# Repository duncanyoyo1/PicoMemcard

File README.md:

# PicoMemcard

PicoMemcard allows you to build your own supercharged PSX Memory Card that can be connected to your computer via USB in order to transfer saves directly to/from your PSX. You can use it to repurpose broken/counterfeit Memory Cards creating a better one using only a Raspberry Pi Pico.

## Features

* Able to faithfully simulate PSX Memory Card
* USB connection to import/export saves
* Allows to copy saves to/from any other memory card (using original PSX file manager)
* Allows to play burned CDs (thanks to [FreePSXBoot])
* Cheaper than an original memory card
* Can store hudreds of memory card images

## Bill of materials

* **Raspberry Pi Pico** (around $5)
* One of:
    * Custom [PicoMemcard PCB](#picomemcard-pcb)
    * Broken/Counterfeit/Original PSX Memory Card (counterfeit ones can be found on AliExpress for around $2-3)
    * PSX/PS2 Controller Cable
    * CAT5 network cable and a bit of creativity.

Basically anything that will allow you to interface with the memory card slot pins will do. If you have a broken contoller you can cut off the cable and use that since controllers and memory cards share the same bus. Of course, plugging your memory card into the controller slot will prevent you from using 2 controllers at the same time.

[This guy] assembled one using a 3d-printed plastic shell and simple CAT5 network cable. I belive this is the cheapest method anybody has come up with until now.

In total building a PicoMemcard wil cost you less than buying a used original Memory Card!

## Video

## PicoMemcard PCB

These are the custom PCBs designed and manufactured specifically for this application. They are not strictly required but make it much easier to build PicoMemcard since you don't need to cut up another memory card and all the soldering pads are easily accessible. All you need to do is to solder the Pico/RP2040-Zero on top of the PCB using a soldering iron.

The Raspberry Pi Pico or RP2040-Zero must sit flush on top of the PCB, fortunately both the Pico and RP2040-Zero provide castellated holes that are easy to solder directly to the PCB's pads. You can use some electrical tape to hold the board in place while you solder the first pins.

I've created a new version of the original PCBs the major difference are:

* The general size is smaller
* A new micro SD card module is supported. This module is smaller, easier to solder and should solve some of the power related issues that were previously present
* Is fitted for the installation of phisical switches used to switch memory card when PicoMemcard+ is used in systems that do not support switching via controller input (e.g. all PS2 models).

The KiCad and Gerber files are available in the repository. If you want to support the project you can request a PCB [from here]. 
Keep in mind that with the PS2 support release that will eventually happen the PCB may undergo some additional changes before its design is finalized.

## PicoMemcard using Memory Card

Raspberry Pi Pico and RP2040-Zero require different pin usage for full compatibility.

The wiring diagrams below show how to build PicoMemcard by wiring respectively a Pico and an RP2040-Zero to a counterfeit memory card. For the other cases (wiring directly to the PSX or using a controller cable) the pins on Pico and RP2040-Zero are the same, the pinout of the PSX/controller can be found on [psx-spx]. The images show the bottom side of the memory card with the cover removed.

The dashed line on the PCB of the memory card is where you should cut a groove deep enough to disconnect the original circuitry from the traces. The yellow squares above the line indicate where you should scrape away the protective film in order to expose the copper traces and solder the wires onto them.

Finally the area at the bottom of the memory card is where you can cut a hole to feed the wires through connecting them to the Pico.
If you are using an RP2040-Zero you can also cut away part of the original Memory Card circuitry to fit it inside the original shell.

The connections in the PicoMemcard+ area are optional and only required if you want to build **PicoMemcard+** (using the optional MicroSD expansion board). Also remember to connect both ground and power to your SD card module (see [MicroSD Module](#microsd-module-for-picomemcard) section for more information).

## PicoMemcard vs PicoMemcard+

Since some features cannot be implmented when using only a Pico/RP2040-Zero but require additional hardware, I've decided to split the project in two versions:

* **PicoMemcard** simplest device to build, only requires a Raspberry Pi Pico / RP2040-Zero
* **PicoMemcard+** more complex and powerful device. Supports additional features such as multiple memory card images but requires additional hardware (namely the MicroSD SPI expansion board).

This approach was choosen because many people want a solution that is as cheap as possible and don't care about additional features. Conversely, others would like to have additional features even if it means spending a bit more money.

The current release of PicoMemcard+ additionally to all the features of PicoMemcard supports:

* Trasparent write-back: the sync operation performed to save new data no longer reults in the memory card appearing as if was briefly disconnected.
* Multiple memory card image switchable through controller input.

## MicroSD Module for PicoMemcard+

There are many variations of MicroSD expansion boards with different pinouts and interfaces. The only requirement for PicoMemcard+ is that the module must provide an SPI interface. SPI interfaces have at least the following pins:

* Chip Select (CS) (sometime also called Slave Select (SS)).
* Clock (SCK or CLK).
* Master Output Slave Input (MISO).
* Master Input Slave Output (MOSI).

In addition you will need to connect power and ground to your module, some modules are design to work with 5V others with 3.3V (or both), luckily for us both voltages are available on Pico and RP2040-Zero as shown in the schematic in the section [above](#picomemcard-using-memory-card). Some module provides additional pins that can be left disconnected.

The new versions of the PCB are designed to use small modules such as this one:

This is mainly due to the following reasons:

* It comes withouth pre-soldered headers which makes it easier to solder onto the PicoMemcard PCB.
* Its smaller form factor allows for more flexibility.
* It should have less power issue than prevously used modules.

A good source for these modules is Aliexpress, in general you can search for `MicroSD SPI Expansion Board` and buy the cheapest one you find.

## Installation

1. Download the latest [release] for your board (Raspberry Pi Pico and RP2040-Zero require different binaries).
2. While pressing the 'BOOTSEL' or 'BOOT' button on your board, plug it into your computer. 
3. Drag and drop the PicoMemcard release onto your Raspberry Pi Pico.
4. PicoMemcard should appear on your PC as a USB drive.
5. Upload a memory card image to your PicoMemcard.

## Transfering Data

Memory card images must be exactly 128KB (131072 bytes) in size. PicoMemcard and PicoMemcard+ only support files with `.MCR` extensions. However, `.MCR` and `.MCD` extensions are interchangable and can be converted to one another simply via renaming.
For other file formats, try using [MemcardRex] for converting to the desired output.

* **PicoMemcard** only supports a single image which must be named exactly `MEMCARD.MCR`.
* **PicoMemcard+** supports hundreds of images. Each image must be named `N.MCR` where `N` is an integer number (e.g. `0.MCR`, `1.MCR`...). On boot your previously loaded image will be reloaded, unless it's a fresh card then `0.MCR` will be loaded.

Inside `docs/images` you can find two memory card images. One has a couple of saves on it so you can test if everything works correctly, the other is completely empty.

## Switching/Creating Images

On **PicoMemcard+** you can switch the active memory card image with the following inputs:

* `START + SELECT + DPAD UP` will switch to the next image (e.g from `1.MCR` to `2.MCR`).
* `START + SELECT + DPAD DOWN` will switch to the previous image (e.g from `1.MCR` to `0.MCR`).

Additionally you can create a new empty memory card image (and automatically switch to it) by pressing  `START + SELECT + TRIANGLE`.

**Attention**: this method only works on PSX if the controller used to provide the input is plugged in the same slot as PicoMemcard (exactly under it). Using a controller from a different slot will have no effect.

Additionally this method does not work on PS2 Memory Cards and Controllers are wired on a different bus.

## Syncing Changes

Generally speaking, new data written to PicoMemcard (e.g. when you save) is permanently stored only after a short period of time (due to hardware limitation). The on board LED indicates whether all changes have been stored or not, in particular:

* On Rapsbery Pi Pico the LED will be on when all changes have been saved, off otherwise.
* On RP2040-Zero the LED will be solid green when all changes have been saved, red otherwise.

Unlike **PicoMemcard+** that tries to write new changes as soon as possible, **PicoMemcard** will generally do it only after a period of inactivity (around 5 seconds). If you want to force **PicoMemcard** to immediately sync you can press `START + SELECT + TRIANGLE`.

**Attention**: after you save your game, make sure to wait for the LED to be solid green before turning off the console otherwise you might lose your more recent progress!

## 3D-Printed Case

I've finally designed a 3D-printable case for the different PicoMemcard PCBs. It helps inserting correctly the PCB and ensuring that the the connection to the PSX is optimal. The same result, albeit more janky, can be achieved using a folded sheet of paper as a spacer.

The cases are designed following a minimalistic approach, they consist of a single piece which holds tightly the PCB using very small clips without requiring any additional hardware. To assemble it, simply slide in the PCB from the back of the case (opposite to the side connecting to the PSX). Cases for the fullsize PCB are designed to support the MicroSD expansion module.

Here is the download for the STL files:

* [Design by DanGiu](https://www.thingiverse.com/thing:5488778)

If you don't like this case you can check out other designs many people have already created! I've not tested them personally but here they are:

* [Design by brik1111](https://www.thingiverse.com/thing:5453156)
* [Design by bbsan2k](https://www.thingiverse.com/thing:5460187)

## Troubleshooting and LED Indicator

Generally speaking the onboard LED will provide a pretty good indication regarding the status of PicoMemcard.

In particular, the RP2040-Zero has RGB LED that provides a more clear output. The Pico on the other hand as only a green LED and different blinking patterns indicate different statuses.

### PicoMemcard Status

| Status | Pico | RP2040-Zero
| --- | --- | --- |
| Failed to read memory card image | Slow blinking led  | Red blinking led
| Data not fully synced (do not turn off PSX)| Led off | Red led (or flashing red and green) |
| Data synced | Led on | Green solid led |

### PicoMemcard+ Status

| Status | Pico | RP2040-Zero
| --- | --- | --- |
| Failed to read SD card | Blinking led  | Red blinking led
| Data not fully synced (do not turn off PSX)| Led off | Red led (or flashing red and green) |
| Data synced | Led on | Green solid led |
| Memory Card image changed | Three fast blinks | Single blue blink |
| Memory Card image not changed (end of list) | Nine fast blinks | Single orange blink |
| New Memory Card image created | Multiple very fast blinks | Single light blue blink |

## General Warnings

I would recommend to never plug PicoMemcard both into the PC (via USB) and the PSX at the same time! Otherwise the 5V provided by USB would end up on the 3.3V rail of the PSX. I'm not really sure if this could cause actual damage but I would avoid risking it.

If you really need to have the Pico plugged into both the USB and PSX (e.g. for debugging purposes), disconnect the 3.3V line from the VBUS pin. In this way you can power on the Pico using a simple USB phone charger or by plugging it into your PC.

As a disclamer, I don't take any responsability for what will happen to your console when using PicoMemcard/PicoMemcard+.

## Project Updates

### 5 February 2023

Sorry everybody but I've been quite inactive on the project lately. Due to a change of job IRL I have less time to work for the moment.
Anyway, behind the scenes I've been trying to add support for PS2 memory card but I'm afraid that will require the addition of an extra hardware component unless I am able to develop an efficient cacheing mechanisms or something similar. Anyway I'll keep working on it when I have free time. I have in mind many improvement for the project and I think the future of it is going to be exciting.

Special thanks to everybody that supported it so far! You are all amazing.

## Design

For people interested in understanding how PicoMemcard works I provide a more extensive explanation in [this post] (although now somewhat outdated).

## Thanks To

* [psx-spx] and Martin "NO$PSX" Korth - PlayStation Specifications and documented Memory Card protocol and filesystem.
* [Andrew J. McCubbin] - Additional information about Memory Card and Controller communication with PSX.
* [littlefs] - Filesystem designed to work on NOR flash used by many microcontrollers, including the Raspberry Pi Pico.
* [ChaN FatFS] - FAT filesystem implementation for embedded devices.
* [Scoppy] - Use your Raspberry Pi Pico as an oscilloscope, very cheap and accurate. Without this I would have not been able to debug many issues.
* [PulseView] - Used to import, visualize and manipulate the data from Scoppy on a PC.

[FreePSXBoot]: https://github.com/brad-lin/FreePSXBoot
[psx-spx]: https://psx-spx.consoledev.net/pinouts/#controller-ports-and-memory-card-ports
[Andrew J. McCubbin]: http://www.emudocs.org/PlayStation/psxcont/
[littlefs]: https://github.com/littlefs-project/littlefs
[ChaN FatFS]: http://elm-chan.org/fsw/ff/00index_e.html
[Scoppy]: https://github.com/fhdm-dev/scoppy
[PulseView]: https://sigrok.org/wiki/PulseView
[release]: https://github.com/dangiu/PicoMemcard/releases/latest
[this post]: https://dangiu.github.io/2022/05/13/picomemcard.html
[from here]: https://forms.gle/f6XHtz6W5fn5qDZV7
[This guy]: https://github.com/MrSVCD/PicoPSX_3D
[MemcardRex]: https://github.com/ShendoXT/memcardrex

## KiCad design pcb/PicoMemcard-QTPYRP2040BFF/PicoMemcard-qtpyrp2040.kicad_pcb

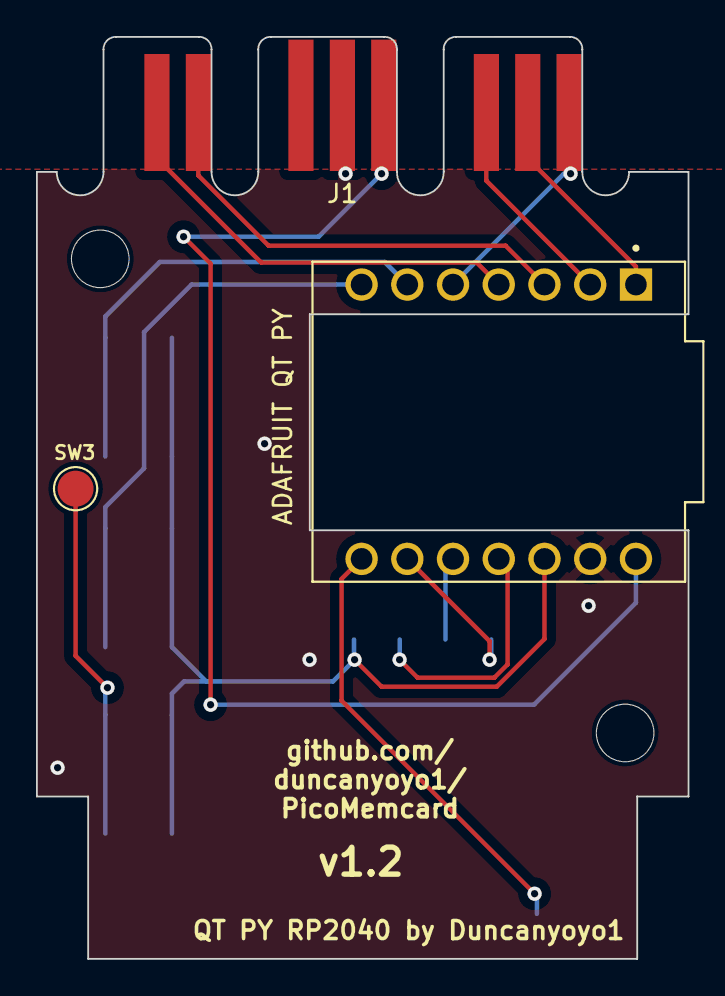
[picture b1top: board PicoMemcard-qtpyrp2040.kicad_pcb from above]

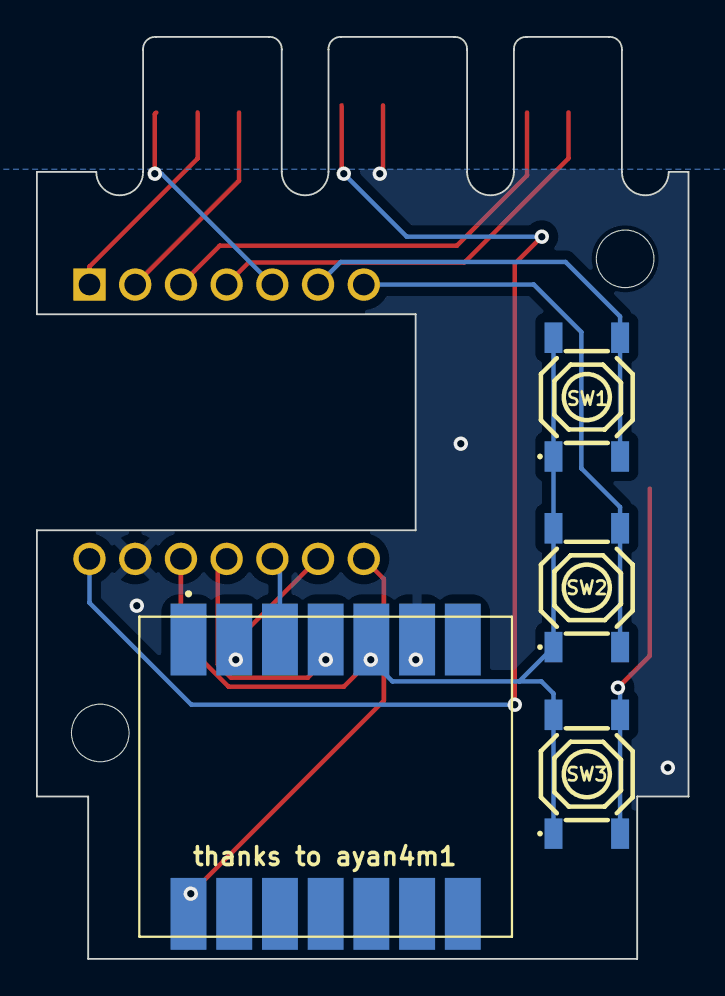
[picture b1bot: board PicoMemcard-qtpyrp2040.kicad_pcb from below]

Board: 2 copper layers, 36.2 x 51.2 mm, 9 parts (4 on the bottom side), 15 nets.

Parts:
H1, H2: M3; MountingHole_3.2mm_M3
J1: PSX Memory Card Interface; MemoryCardConnector
SW1, SW2, SW3: TS-1187A-B-A-B; SW-SMD_4P-L5.1-W5.1-P3.70-LS6.5-TL-2
TP1: GP23; TestPoint_Pad_D2.0mm
U1: QT PY SD BFF; MODULE_ADAFRUIT_QT_PY_BFF
U2: ADAFRUIT QT PY; MODULE_ADAFRUIT_QT_PY

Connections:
+3V3: SW1.1 (A), SW1.2 (B), SW2.1 (A), SW2.2 (B), SW3.1 (A), SW3.2 (B), U1.5 (3V3), U2.12 (3V3)
+5V: J1.5 (5V), U2.14 (5V)
ACK: J1.8 (ACK), U2.5 (D4/SDA)
CLK: J1.7 (CLK), U2.1 (A0/D0/DAC)
CMD: J1.2 (CMD), U2.3 (A2/D2)
CS: U1.14 (CS), U2.8 (A7/D7/RX)
DAT: J1.1 (DAT), U2.4 (A3/D3)
GND: J1.4 (GND), U1.6 (GND), U2.13 (GND)
GP26: SW1.3 (C), SW1.4 (D), U2.6 (D5/SCL)
GP27: SW2.3 (C), SW2.4 (D), U2.7 (A6/D6/TX)
GP28: SW3.3 (C), SW3.4 (D), TP1.1
MISO: U1.3 (MISO), U2.10 (A9/D9/MISO)
MOSI: U1.4 (MOSI), U2.11 (A10/D10/MOSI)
SCK: U1.2 (SCK), U2.9 (A8/D8/SCK)
SEL: J1.6 (SEL), U2.2 (A1/D1)

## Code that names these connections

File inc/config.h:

#ifndef __CONFIG_H__
#define __CONFIG_H__

/* Global configuration options for PicoMemcard */
#define TUD_MOUNT_TIMEOUT	3000			// max time (in ms) before giving up on MSC mode (USB) and starting memcard simulation
#define MSC_WRITE_SYNC_TIMEOUT 1 * 1000		// time (in ms) expired since last MSC write before exporting RAM disk into LFS
#define IDLE_AUTOSYNC_TIMEOUT 5 * 1000		// time (in ms) the memory card must be inactive before automatic sync from RAM to LFS
#define MAX_MC_FILENAME_LEN	32				// max length of memory card file name
#define MAX_MC_INDEX	255					// maximum number of different mc images
#define MC_RECONNECT_TIME	1000				// time (in ms) the memory card stays disconnected when simulating reconnection

/* Board targeted by build */
//#define PICO
//#define WAVESHARE_RP2040_ZERO
#define ADAFRUIT_QTPY_RP2040
#ifndef PICO_BOARD
#define PICO
#endif

/* PSX Interface Pinout */
#ifdef PICO
	#define PIN_DAT 5
	#define PIN_CMD PIN_DAT + 1		// must be immediately after PIN_DAT
	#define PIN_SEL PIN_CMD + 1		// must be immediately after PIN_CMD
	#define PIN_CLK PIN_SEL + 1		// must be immediately after PIN_SEL
	#define PIN_ACK 9
#endif

#ifdef WAVESHARE_RP2040_ZERO
	#define PIN_DAT 9
	#define PIN_CMD PIN_DAT + 1		// must be immediately after PIN_DAT
	#define PIN_SEL PIN_CMD + 1		// must be immediately after PIN_CMD
	#define PIN_CLK PIN_SEL + 1		// must be immediately after PIN_SEL
	#define PIN_ACK 13
#endif

#ifdef ADAFRUIT_QTPY_RP2040
    #define PIN_CLK 2
    #define PIN_SEL PIN_CLK + 1	   // must be immediately after PIN_CLK
    #define PIN_CMD PIN_SEL + 1    // must be immediately after PIN_SEL
    #define PIN_DAT PIN_CMD + 1    // must be immediately after PIN_CMD
    #define PIN_ACK 17
#endif

/* SD Card Configuration */
#define BLOCK_SIZE	512				// SD card communicate using only 512 block size for consistency
#define BAUD_RATE	5000 * 1000
#ifdef PICO
	#define PIN_MISO	16
	#define PIN_MOSI	19
	#define PIN_SCK		18
	#define PIN_SS		17
#endif

#ifdef WAVESHARE_RP2040_ZERO
	#define PIN_MISO	0
	#define PIN_MOSI	3
	#define PIN_SCK		2
	#define PIN_SS		1
#endif

#ifdef ADAFRUIT_QTPY_RP2040
	#define PIN_MISO	9
	#define PIN_MOSI	10
	#define PIN_SCK		8
	#define PIN_SS		7
#endif

#endif

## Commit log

2023-08-28 Add QT PY RP2040 Board and Gerbers, update QTPY PR to build on Main
2023-08-31 Connect 3V3 NET to MicroSD BFF
2023-09-01 Update gitignore and PCB revision
2023-09-13 Fix build maybe? No idea anymore pico-sdk is terrible
2023-09-13 GitIgnore
2023-09-13 Pico-sdk y
2023-09-13 gitmodules
2023-09-16 Fix QTPY MicroSD BFF Footprint
2024-02-18 Update some pcb files, last known good
2024-02-18 Update all files
